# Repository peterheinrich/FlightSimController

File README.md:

# Overview
This small project implements a controller board intended for use in DIY flight simulator cockpits. The goal of the project is to create a versatile
hardware component suitable for a variety of simulated instruments (from buttons, dials and lights to glass cockpits), using a common bus 
interconnect and a common programming model and environment.

# Basic Requirements
- Flexible I/O (3.3 V digital I/O, high current H-bridge for stepper motors, analog input for sliders and potentiometers).
- Raspberry Pi CM4 connectors with HDMI/USB and parallel display connectors for resolutions (320x240 to 4k)
- RP2040 microcontroller for all low-spped I/O
- RS485 bus connector with integrated power supply via D-SUB-9 connector

# Current Project State
!!! EXPERIMENTAL, DESIGN ONLY !!!

Board Schematic:
[Schematic](/assets/FlightSimController-Schematics.pdf)

Rendered board view (front):

Rendered board view (back):

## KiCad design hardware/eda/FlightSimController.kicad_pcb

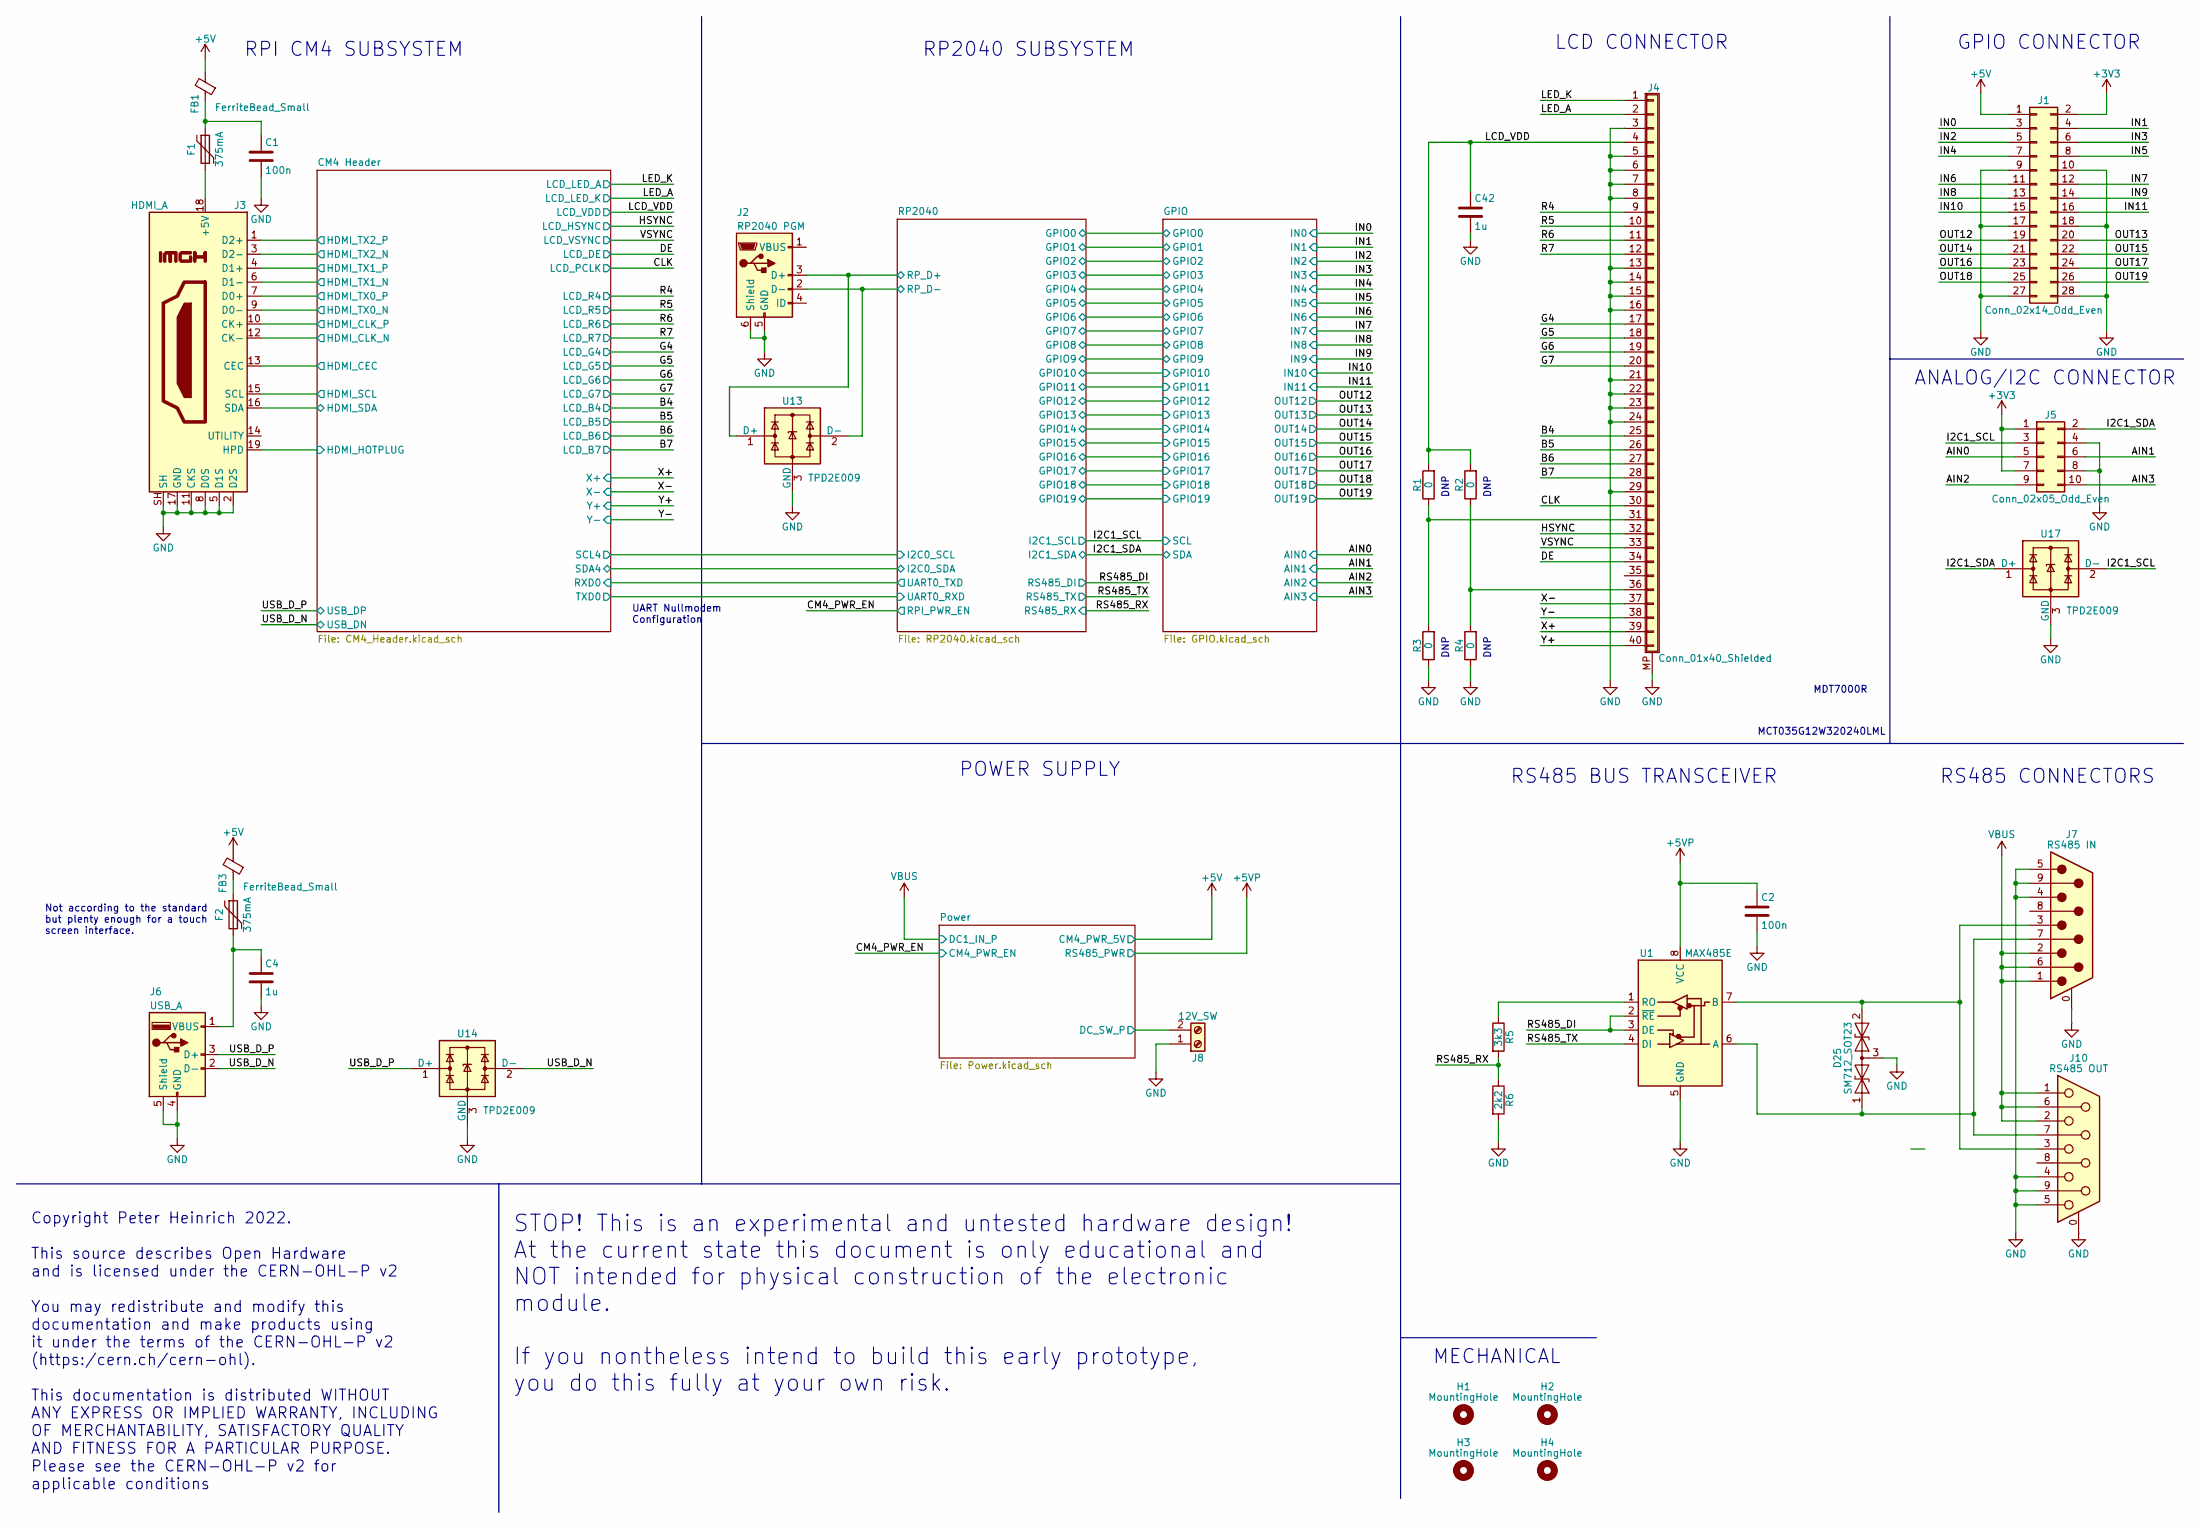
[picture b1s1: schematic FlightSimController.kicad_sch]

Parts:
C1, C2: 100n; C_0603_1608Metric_Pad1.08x0.95mm_HandSolder; MPN C0603C104K4RACTU
C4, C42: 1u; C_0603_1608Metric_Pad1.08x0.95mm_HandSolder; MPN CC0603KRX5R6BB105
D25: SM712_SOT23; SOT-23; MPN SM712-02HTG
F1, F2: 375mA; Fuse_1210_3225Metric_Pad1.42x2.65mm_HandSolder; MPN MCCFB1206TFF/375
FB1, FB3: FerriteBead_Small; L_0805_2012Metric; MPN BLM21PG221SN1D
H1, H2, H3, H4: MountingHole; MountingHole_3.2mm_M3_DIN965
J1: Conn_02x14_Odd_Even; PinHeader_2x14_P2.54mm_Vertical; MPN 68691-440HLF
J2: RP2040 PGM; USB_Micro-B_Wuerth_614105150721_Vertical_CircularHoles; MPN 614105150721
J3: HDMI_A; HDMI_A_Molex_208658-1001_Horizontal; MPN 208658-1001
J4: Conn_01x40_Shielded; TE_4-1734839-0_1x40-1MP_P0.5mm_Horizontal; MPN 4-1734839-0
J5: Conn_02x05_Odd_Even; PinHeader_2x05_P2.54mm_Vertical; MPN 826925-5
J6: USB_A; USB_A_Molex_67643_Horizontal; MPN 67643-0910
J7: RS485 IN; DSUB-9_Male_Vertical_P2.77x2.84mm_MountingHoles; MPN L777TSEG09POL2RM8
J8: 12V_SW; TerminalBlock_bornier-2_P5.08mm; MPN PM5.08/2/90 BLK
J10: RS485 OUT; DSUB-9_Female_Vertical_P2.77x2.84mm_MountingHoles; MPN L77TSEH09SOL2RM8
R1, R2, R3, R4: 0; R_0603_1608Metric_Pad0.98x0.95mm_HandSolder; MPN RC0603JR-070RL
R5: 3k3; R_0603_1608Metric_Pad0.98x0.95mm_HandSolder; MPN RC0603FR-073K3L
R6: 2k2; R_0603_1608Metric_Pad0.98x0.95mm_HandSolder; MPN RC0603FR-132K2L
U1: MAX485E; SOIC-8_3.9x4.9mm_P1.27mm; MPN MAX485CSA+
U13, U14, U17: TPD2E009; SOT-23; MPN TPD2E009DBZR

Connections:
+3V3: J1.2, J5.1, J5.7; also elsewhere on the board
+5V: FB1.2, FB3.2, J1.1; also elsewhere on the board
+5VP: C2.1, U1.8 (VCC); also elsewhere on the board
/AIN0: J5.5; also elsewhere on the board
/AIN1: J5.6; also elsewhere on the board
/AIN2: J5.9; also elsewhere on the board
/AIN3: J5.10; also elsewhere on the board
/B4: J4.25; also elsewhere on the board
/B5: J4.26; also elsewhere on the board
/B6: J4.27; also elsewhere on the board
/B7: J4.28; also elsewhere on the board
/CLK: J4.30; also elsewhere on the board
/CM4 Header/HDMI_CEC: J3.13 (CEC); also elsewhere on the board
/CM4 Header/HDMI_CLK_N: J3.12 (CK-); also elsewhere on the board
/CM4 Header/HDMI_CLK_P: J3.10 (CK+); also elsewhere on the board
/CM4 Header/HDMI_SCL: J3.15 (SCL); also elsewhere on the board
/CM4 Header/HDMI_SDA: J3.16 (SDA); also elsewhere on the board
/CM4 Header/HDMI_TX0_N: J3.9 (D0-); also elsewhere on the board
/CM4 Header/HDMI_TX0_P: J3.7 (D0+); also elsewhere on the board
/CM4 Header/HDMI_TX1_N: J3.6 (D1-); also elsewhere on the board
/CM4 Header/HDMI_TX1_P: J3.4 (D1+); also elsewhere on the board
/CM4 Header/HDMI_TX2_N: J3.3 (D2-); also elsewhere on the board
/CM4 Header/HDMI_TX2_P: J3.1 (D2+); also elsewhere on the board
/DE: J4.34; also elsewhere on the board
/G4: J4.17; also elsewhere on the board
/G5: J4.18; also elsewhere on the board
/G6: J4.19; also elsewhere on the board
/G7: J4.20; also elsewhere on the board
/HDMI_HOTPLUG: J3.19 (HPD)
/HSYNC: J4.32; also elsewhere on the board
/I2C1_SCL: J5.3, U17.2 (D-); also elsewhere on the board
/I2C1_SDA: J5.2, U17.1 (D+); also elsewhere on the board
/IN0: J1.3; also elsewhere on the board
/IN1: J1.4; also elsewhere on the board
/IN2: J1.5; also elsewhere on the board
/IN3: J1.6; also elsewhere on the board
/IN4: J1.7; also elsewhere on the board
/IN5: J1.8; also elsewhere on the board
/IN6: J1.11; also elsewhere on the board
/IN7: J1.12; also elsewhere on the board
/IN8: J1.13; also elsewhere on the board
/IN9: J1.14; also elsewhere on the board
/IN10: J1.15; also elsewhere on the board
/IN11: J1.16; also elsewhere on the board
/LCD_VDD: C42.1, J4.4, R1.2, R2.2; also elsewhere on the board
/LED_A: J4.2; also elsewhere on the board
/LED_K: J4.1; also elsewhere on the board
/OUT12: J1.19; also elsewhere on the board
/OUT13: J1.20; also elsewhere on the board
/OUT14: J1.21; also elsewhere on the board
/OUT15: J1.22; also elsewhere on the board
/OUT16: J1.23; also elsewhere on the board
/OUT17: J1.24; also elsewhere on the board
/OUT18: J1.25; also elsewhere on the board
/OUT19: J1.26; also elsewhere on the board
/Power/DC_SW_P: J8.2; also elsewhere on the board
/R4: J4.9; also elsewhere on the board
/R5: J4.10; also elsewhere on the board
/R6: J4.11; also elsewhere on the board
/R7: J4.12; also elsewhere on the board
/RP2040/RP_D+: J2.3 (D+), U13.1 (D+); also elsewhere on the board
/RP2040/RP_D-: J2.2 (D-), U13.2 (D-); also elsewhere on the board
/RS485_DI: U1.2 (~RE), U1.3 (DE); also elsewhere on the board
/RS485_RX: R5.2, R6.1; also elsewhere on the board
/RS485_TX: U1.4 (DI); also elsewhere on the board
/USB_D_N: J6.2 (D-), U14.2 (D-); also elsewhere on the board
/USB_D_P: J6.3 (D+), U14.1 (D+); also elsewhere on the board
/VSYNC: J4.33; also elsewhere on the board
/X+: J4.39; also elsewhere on the board
/X-: J4.37; also elsewhere on the board
/Y+: J4.40; also elsewhere on the board
/Y-: J4.38; also elsewhere on the board
GND: C1.2, C2.2, C4.2, C42.2, D25.3 (common), J1.9, J1.10, J1.17, J1.18, J1.27, J1.28, J2.5 (GND), J2.6 (Shield), J3.2 (D2S), J3.5 (D1S), J3.8 (D0S), J3.11 (CKS), J3.17 (GND), J3.SH, J4.3, J4.5, J4.6, J4.7, J4.8, J4.13, J4.14, J4.15, J4.16, J4.21, J4.22, J4.23, J4.24, J4.29, J4.MP (Shield), J5.4, J5.8, J6.4 (GND), J6.5 (Shield), J7.0 (PAD), J7.4, J7.5, J7.9, J8.1, J10.0 (PAD), J10.4, J10.5, J10.9, R3.1, R4.1, R6.2, U1.5 (GND), U13.3 (GND), U14.3 (GND), U17.3 (GND); also elsewhere on the board
unnamed: C1.1, F1.1, FB1.1
unnamed: C4.1, F2.2, J6.1 (VBUS)
unnamed: D25.1 (A1), J7.7, J10.7, U1.6 (A)
unnamed: D25.2 (A2), J7.3, J10.3, U1.7 (B)
unnamed: F1.2, J3.18 (+5V)
unnamed: F2.1, FB3.1
unnamed: J4.31, R1.1, R3.2
unnamed: J4.36, R2.1, R4.2
unnamed: R5.1, U1.1 (RO)
VBUS: J7.1, J7.2, J7.6, J10.1, J10.2, J10.6; also elsewhere on the board

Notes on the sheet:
UART Nullmodem Configuration
DNP
RPI CM4 SUBSYSTEM
MCT035G12W320240LML
LCD CONNECTOR
GPIO CONNECTOR
POWER SUPPLY
Not according to the standard but plenty enough for a touch screen interface.
Copyright Peter Heinrich 2022. This source describes Open Hardware and is licensed under the CERN-OHL-P v2 You may redistribute and modify this documentation and make products using it under the terms of the CERN-OHL-P v2 (https:/cern.ch/cern-ohl). This documentation is distributed WITHOUT ANY EXPR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
RS485 CONNECTORS
MDT7000R
MECHANICAL
ANALOG/I2C CONNECTOR
RS485 BUS TRANSCEIVER
RP2040 SUBSYSTEM
STOP! This is an experimental and untested hardware design! At the current state this document is only educational and NOT intended for physical construction of the electronic module. If you nontheless intend to build this early prototype, you do this fully at your own risk.

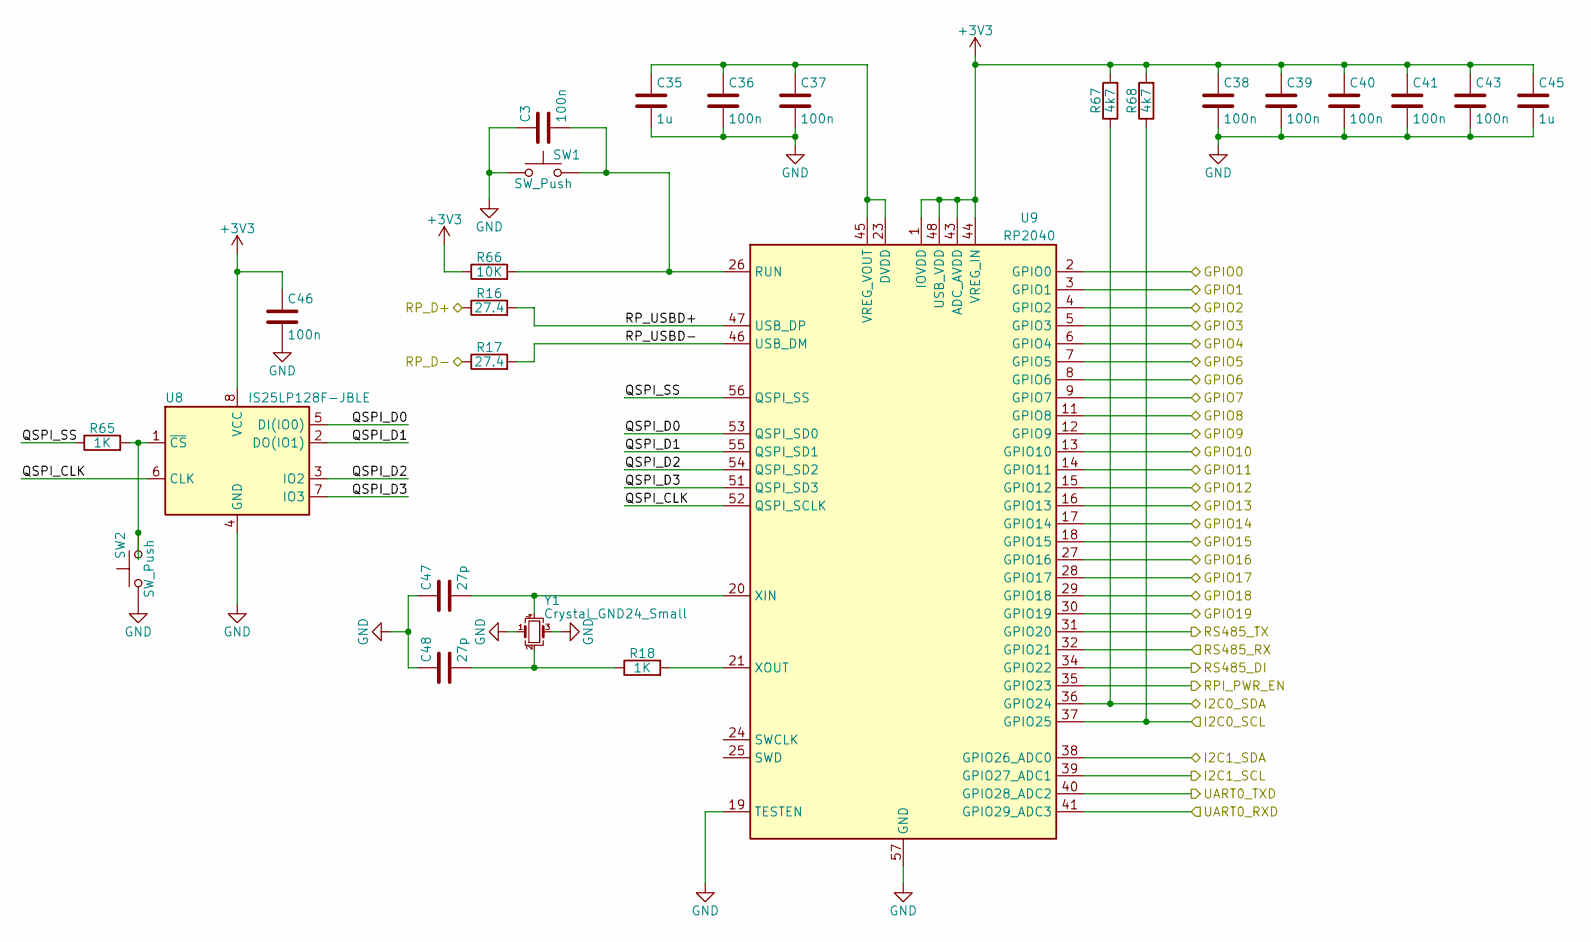
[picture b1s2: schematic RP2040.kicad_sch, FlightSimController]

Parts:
C3, C36, C37, C38, C39, C40, C41, C43, C46: 100n; C_0603_1608Metric_Pad1.08x0.95mm_HandSolder; MPN C0603C104K4RACTU
C35, C45: 1u; C_0603_1608Metric_Pad1.08x0.95mm_HandSolder; MPN CC0603KRX5R6BB105
C47, C48: 27p; C_0603_1608Metric_Pad1.08x0.95mm_HandSolder; MPN C0603C270K5GACTU
R16, R17: 27.4; R_0603_1608Metric_Pad0.98x0.95mm_HandSolder; MPN RC0603FR-0727R4L
R18, R65: 1K; R_0603_1608Metric_Pad0.98x0.95mm_HandSolder; MPN RC0603JR-071KL
R66: 10K; R_0603_1608Metric_Pad0.98x0.95mm_HandSolder; MPN RC0603FR-0710KL
R67, R68: 4k7; R_0603_1608Metric_Pad0.98x0.95mm_HandSolder; MPN RC0603FR-074K7L.
SW1, SW2: SW_Push; SW_Push_1P1T_NO_CK_KSC7xxJ; MPN KSC721J LFS
U8: IS25LP128F-JBLE; SOIC-8_5.23x5.23mm_P1.27mm; MPN IS25LP128F-JBLE
U9: RP2040; QFN-56-1EP_7x7mm_P0.4mm_EP3.2x3.2mm; MPN RP2040CT
Y1: Crystal_GND24_Small; Crystal_SMD_Abracon_ABM8G-4Pin_3.2x2.5mm; MPN ABM8G-12.000MHZ-18-D2Y-T

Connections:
+3V3: C38.1, C39.1, C40.1, C41.1, C43.1, C45.1, C46.1, R66.1, R67.2, R68.2, U8.8 (VCC), U9.1 (IOVDD), U9.10 (IOVDD), U9.22 (IOVDD), U9.33 (IOVDD), U9.42 (IOVDD), U9.43 (ADC_AVDD), U9.44 (VREG_IN), U9.48 (USB_VDD), U9.49 (IOVDD); also elsewhere on the board
/CM4 Header/RXD0: U9.40 (GPIO28_ADC2); also elsewhere on the board
/CM4 Header/SCL4: R68.1, U9.37 (GPIO25); also elsewhere on the board
/CM4 Header/SDA4: R67.1, U9.36 (GPIO24); also elsewhere on the board
/CM4 Header/TXD0: U9.41 (GPIO29_ADC3); also elsewhere on the board
/CM4_PWR_EN: U9.35 (GPIO23); also elsewhere on the board
/GPIO/GPIO0: U9.2 (GPIO0); also elsewhere on the board
/GPIO/GPIO1: U9.3 (GPIO1); also elsewhere on the board
/GPIO/GPIO2: U9.4 (GPIO2); also elsewhere on the board
/GPIO/GPIO3: U9.5 (GPIO3); also elsewhere on the board
/GPIO/GPIO4: U9.6 (GPIO4); also elsewhere on the board
/GPIO/GPIO5: U9.7 (GPIO5); also elsewhere on the board
/GPIO/GPIO6: U9.8 (GPIO6); also elsewhere on the board
/GPIO/GPIO7: U9.9 (GPIO7); also elsewhere on the board
/GPIO/GPIO8: U9.11 (GPIO8); also elsewhere on the board
/GPIO/GPIO9: U9.12 (GPIO9); also elsewhere on the board
/GPIO/GPIO10: U9.13 (GPIO10); also elsewhere on the board
/GPIO/GPIO11: U9.14 (GPIO11); also elsewhere on the board
/GPIO/GPIO12: U9.15 (GPIO12); also elsewhere on the board
/GPIO/GPIO13: U9.16 (GPIO13); also elsewhere on the board
/GPIO/GPIO14: U9.17 (GPIO14); also elsewhere on the board
/GPIO/GPIO15: U9.18 (GPIO15); also elsewhere on the board
/GPIO/GPIO16: U9.27 (GPIO16); also elsewhere on the board
/GPIO/GPIO17: U9.28 (GPIO17); also elsewhere on the board
/GPIO/GPIO18: U9.29 (GPIO18); also elsewhere on the board
/GPIO/GPIO19: U9.30 (GPIO19); also elsewhere on the board
/I2C1_SCL: U9.39 (GPIO27_ADC1); also elsewhere on the board
/I2C1_SDA: U9.38 (GPIO26_ADC0); also elsewhere on the board
/RP2040/QSPI_CLK: U8.6 (CLK), U9.52 (QSPI_SCLK)
/RP2040/QSPI_D0: U8.5 (DI(IO0)), U9.53 (QSPI_SD0)
/RP2040/QSPI_D1: U8.2 (DO(IO1)), U9.55 (QSPI_SD1)
/RP2040/QSPI_D2: U8.3 (IO2), U9.54 (QSPI_SD2)
/RP2040/QSPI_D3: U8.7 (IO3), U9.51 (QSPI_SD3)
/RP2040/QSPI_SS: R65.1, U9.56 (QSPI_SS)
/RP2040/RP_D+: R16.1; also elsewhere on the board
/RP2040/RP_D-: R17.1; also elsewhere on the board
/RP2040/RP_USBD+: R16.2, U9.47 (USB_DP)
/RP2040/RP_USBD-: R17.2, U9.46 (USB_DM)
/RS485_DI: U9.34 (GPIO22); also elsewhere on the board
/RS485_RX: U9.32 (GPIO21); also elsewhere on the board
/RS485_TX: U9.31 (GPIO20); also elsewhere on the board
GND: C3.1, C35.2, C36.2, C37.2, C38.2, C39.2, C40.2, C41.2, C43.2, C45.2, C46.2, C47.1, C48.1, SW1.1, SW2.1, U8.4 (GND), U9.19 (TESTEN), U9.57 (GND), Y1.1, Y1.3; also elsewhere on the board
unnamed: C3.2, R66.2, SW1.2, U9.26 (RUN)
unnamed: C35.1, C36.1, C37.1, U9.23 (DVDD), U9.45 (VREG_VOUT), U9.50 (DVDD)
unnamed: C47.2, U9.20 (XIN), Y1.4
unnamed: C48.2, R18.1, Y1.2
unnamed: R18.2, U9.21 (XOUT)
unnamed: R65.2, SW2.2, U8.1 (~CS)

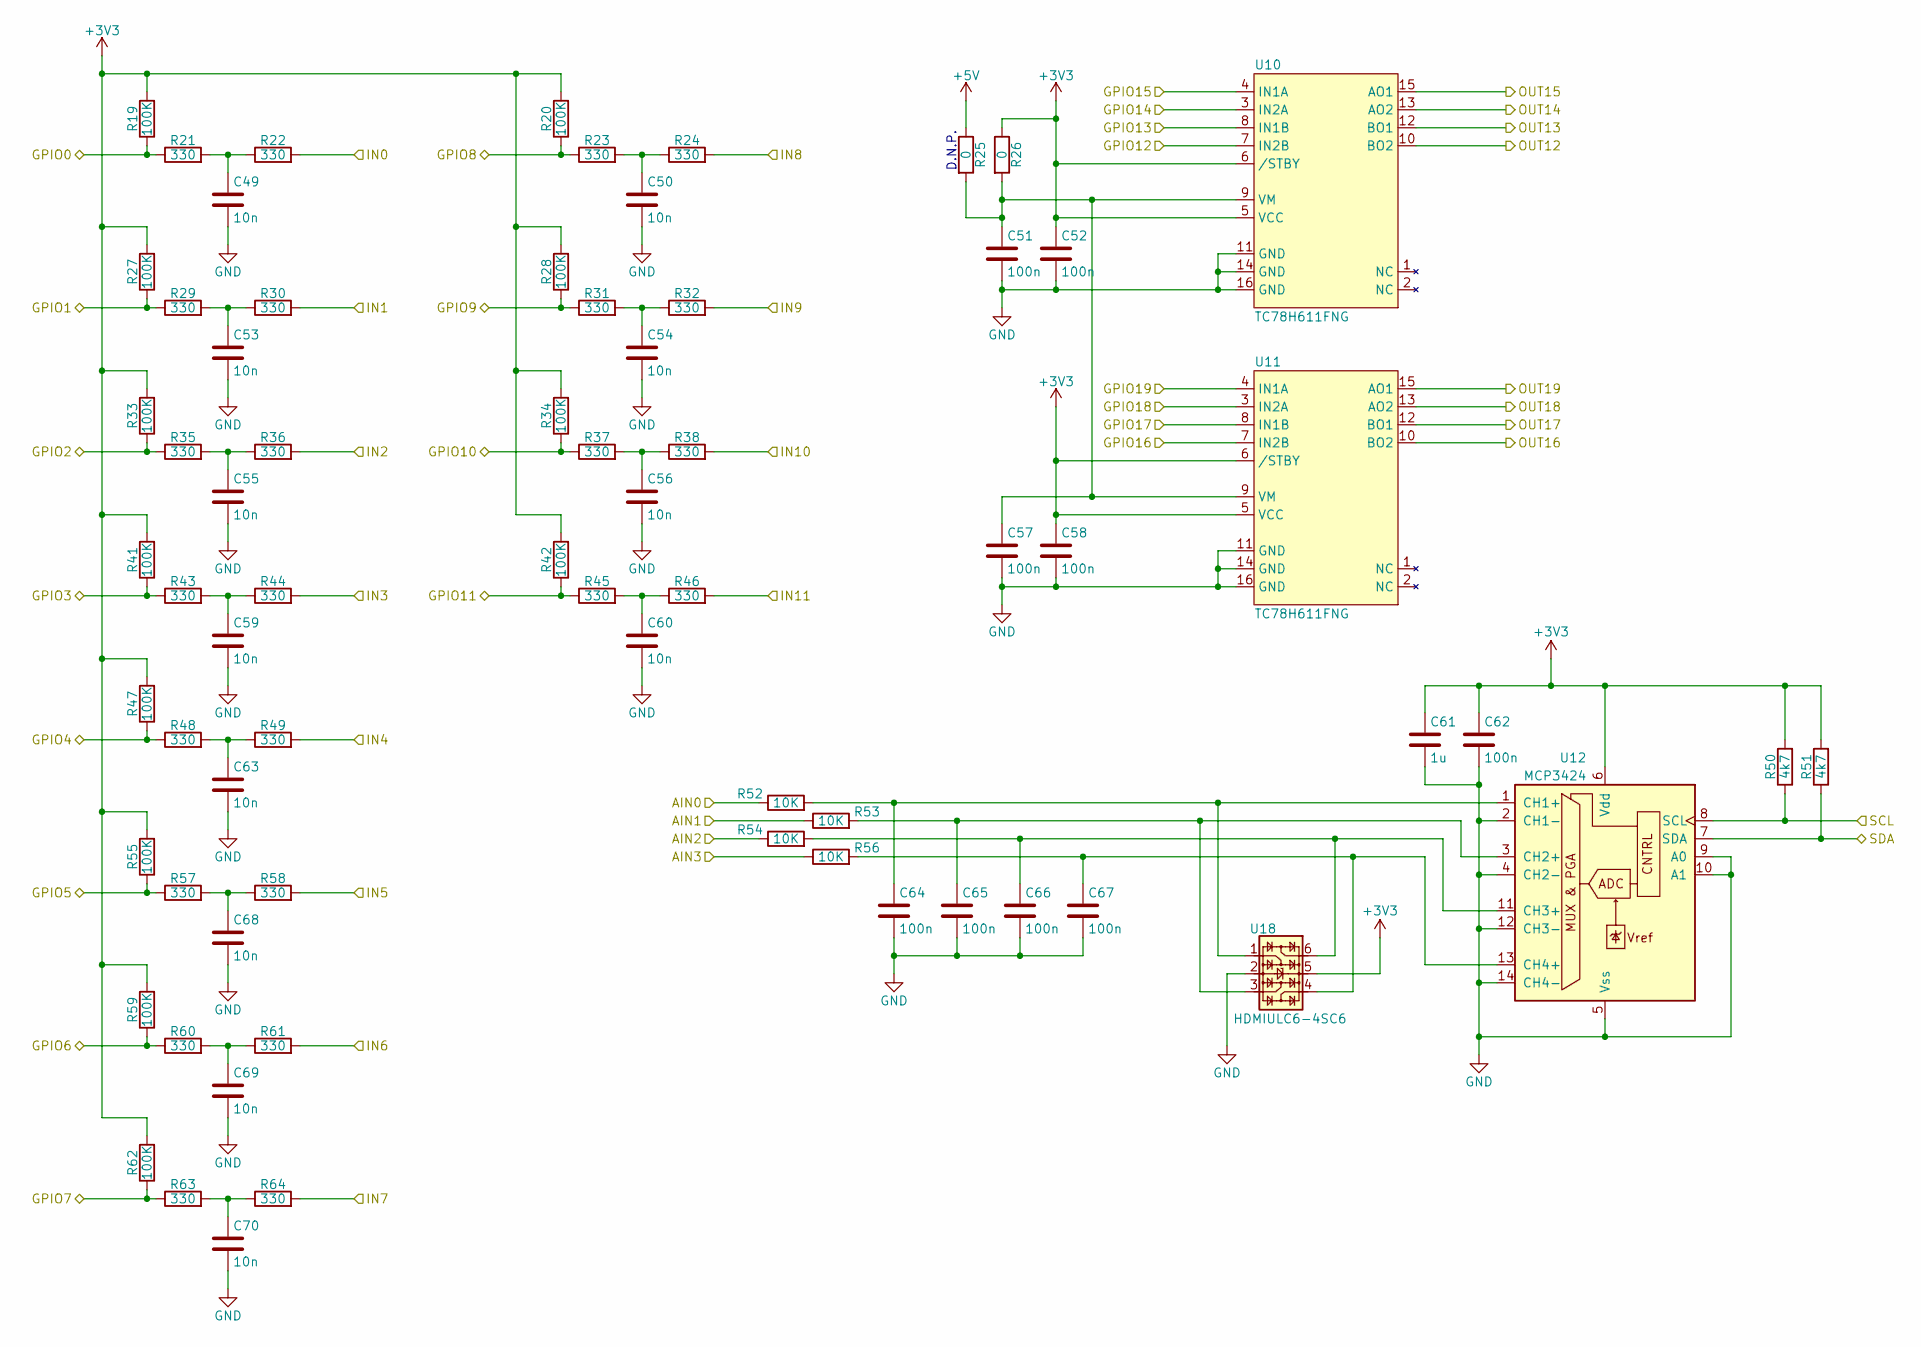
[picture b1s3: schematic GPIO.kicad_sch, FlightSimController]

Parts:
C49, C50, C53, C54, C55, C56, C59, C60, C63, C68, C69, C70: 10n; C_0603_1608Metric_Pad1.08x0.95mm_HandSolder; MPN CC0603KRX7R9BB103
C51, C52, C57, C58, C62, C64, C65, C66, C67: 100n; C_0603_1608Metric_Pad1.08x0.95mm_HandSolder; MPN C0603C104K4RACTU
C61: 1u; C_0603_1608Metric_Pad1.08x0.95mm_HandSolder; MPN CC0603KRX5R6BB105
R19, R20, R27, R28, R33, R34, R41, R42, R47, R55, R59, R62: 100K; R_0603_1608Metric_Pad0.98x0.95mm_HandSolder; MPN RC0603FR-13100KL
R21, R22, R23, R24, R29, R30, R31, R32, R35, R36, R37, R38, R43, R44, R45, R46, R48, R49, R57, R58, R60, R61, R63, R64: 330; R_0603_1608Metric_Pad0.98x0.95mm_HandSolder; MPN RC0603FR-07330RL
R25, R26: 0; R_0603_1608Metric_Pad0.98x0.95mm_HandSolder; MPN RC0603JR-070RL
R50, R51: 4k7; R_0603_1608Metric_Pad0.98x0.95mm_HandSolder; MPN RC0603FR-074K7L.
R52, R53, R54, R56: 10K; R_0603_1608Metric_Pad0.98x0.95mm_HandSolder; MPN RC0603FR-0710KL
U10, U11: TC78H611FNG; TSSOP-16_4.4x5mm_P0.65mm; MPN TC78H611FNG(O,EL)
U12: MCP3424; SOIC-14_3.9x8.7mm_P1.27mm; MPN MCP3424-E/SL
U18: HDMIULC6-4SC6; SOT-23-6; MPN HDMIULC6-4SC6

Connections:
+3V3: C52.1, C58.1, C61.1, C62.1, R19.2, R20.2, R26.1, R27.2, R28.2, R33.2, R34.2, R41.2, R42.2, R47.2, R50.2, R51.2, R55.2, R59.2, R62.2, U10.5 (VCC), U10.6 (/STBY), U11.5 (VCC), U11.6 (/STBY), U12.6 (Vdd), U18.5; also elsewhere on the board
+5V: R25.1; also elsewhere on the board
/AIN0: R52.1; also elsewhere on the board
/AIN1: R53.1; also elsewhere on the board
/AIN2: R54.1; also elsewhere on the board
/AIN3: R56.1; also elsewhere on the board
/GPIO/GPIO0: R19.1, R21.1; also elsewhere on the board
/GPIO/GPIO1: R27.1, R29.1; also elsewhere on the board
/GPIO/GPIO2: R33.1, R35.1; also elsewhere on the board
/GPIO/GPIO3: R41.1, R43.1; also elsewhere on the board
/GPIO/GPIO4: R47.1, R48.1; also elsewhere on the board
/GPIO/GPIO5: R55.1, R57.1; also elsewhere on the board
/GPIO/GPIO6: R59.1, R60.1; also elsewhere on the board
/GPIO/GPIO7: R62.1, R63.1; also elsewhere on the board
/GPIO/GPIO8: R20.1, R23.1; also elsewhere on the board
/GPIO/GPIO9: R28.1, R31.1; also elsewhere on the board
/GPIO/GPIO10: R34.1, R37.1; also elsewhere on the board
/GPIO/GPIO11: R42.1, R45.1; also elsewhere on the board
/GPIO/GPIO12: U10.7 (IN2B); also elsewhere on the board
/GPIO/GPIO13: U10.8 (IN1B); also elsewhere on the board
/GPIO/GPIO14: U10.3 (IN2A); also elsewhere on the board
/GPIO/GPIO15: U10.4 (IN1A); also elsewhere on the board
/GPIO/GPIO16: U11.7 (IN2B); also elsewhere on the board
/GPIO/GPIO17: U11.8 (IN1B); also elsewhere on the board
/GPIO/GPIO18: U11.3 (IN2A); also elsewhere on the board
/GPIO/GPIO19: U11.4 (IN1A); also elsewhere on the board
/I2C1_SCL: R50.1, U12.8 (SCL); also elsewhere on the board
/I2C1_SDA: R51.1, U12.7 (SDA); also elsewhere on the board
/IN0: R22.2; also elsewhere on the board
/IN1: R30.2; also elsewhere on the board
/IN2: R36.2; also elsewhere on the board
/IN3: R44.2; also elsewhere on the board
/IN4: R49.2; also elsewhere on the board
/IN5: R58.2; also elsewhere on the board
/IN6: R61.2; also elsewhere on the board
/IN7: R64.2; also elsewhere on the board
/IN8: R24.2; also elsewhere on the board
/IN9: R32.2; also elsewhere on the board
/IN10: R38.2; also elsewhere on the board
/IN11: R46.2; also elsewhere on the board
/OUT12: U10.10 (BO2); also elsewhere on the board
/OUT13: U10.12 (BO1); also elsewhere on the board
/OUT14: U10.13 (AO2); also elsewhere on the board
/OUT15: U10.15 (AO1); also elsewhere on the board
/OUT16: U11.10 (BO2); also elsewhere on the board
/OUT17: U11.12 (BO1); also elsewhere on the board
/OUT18: U11.13 (AO2); also elsewhere on the board
/OUT19: U11.15 (AO1); also elsewhere on the board
GND: C49.2, C50.2, C51.2, C52.2, C53.2, C54.2, C55.2, C56.2, C57.2, C58.2, C59.2, C60.2, C61.2, C62.2, C63.2, C64.2, C65.2, C66.2, C67.2, C68.2, C69.2, C70.2, U10.11 (GND), U10.14 (GND), U10.16 (GND), U11.11 (GND), U11.14 (GND), U11.16 (GND), U12.2 (CH1-), U12.4 (CH2-), U12.5 (Vss), U12.9 (A0), U12.10 (A1), U12.12 (CH3-), U12.14 (CH4-), U18.2; also elsewhere on the board
unnamed: C49.1, R21.2, R22.1
unnamed: C50.1, R23.2, R24.1
unnamed: C51.1, C57.1, R25.2, R26.2, U10.9 (VM), U11.9 (VM)
unnamed: C53.1, R29.2, R30.1
unnamed: C54.1, R31.2, R32.1
unnamed: C55.1, R35.2, R36.1
unnamed: C56.1, R37.2, R38.1
unnamed: C59.1, R43.2, R44.1
unnamed: C60.1, R45.2, R46.1
unnamed: C63.1, R48.2, R49.1
unnamed: C64.1, R52.2, U12.1 (CH1+), U18.1
unnamed: C65.1, R53.2, U12.3 (CH2+), U18.3
unnamed: C66.1, R54.2, U12.11 (CH3+), U18.6
unnamed: C67.1, R56.2, U12.13 (CH4+), U18.4
unnamed: C68.1, R57.2, R58.1
unnamed: C69.1, R60.2, R61.1
unnamed: C70.1, R63.2, R64.1

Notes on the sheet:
D.N.P.

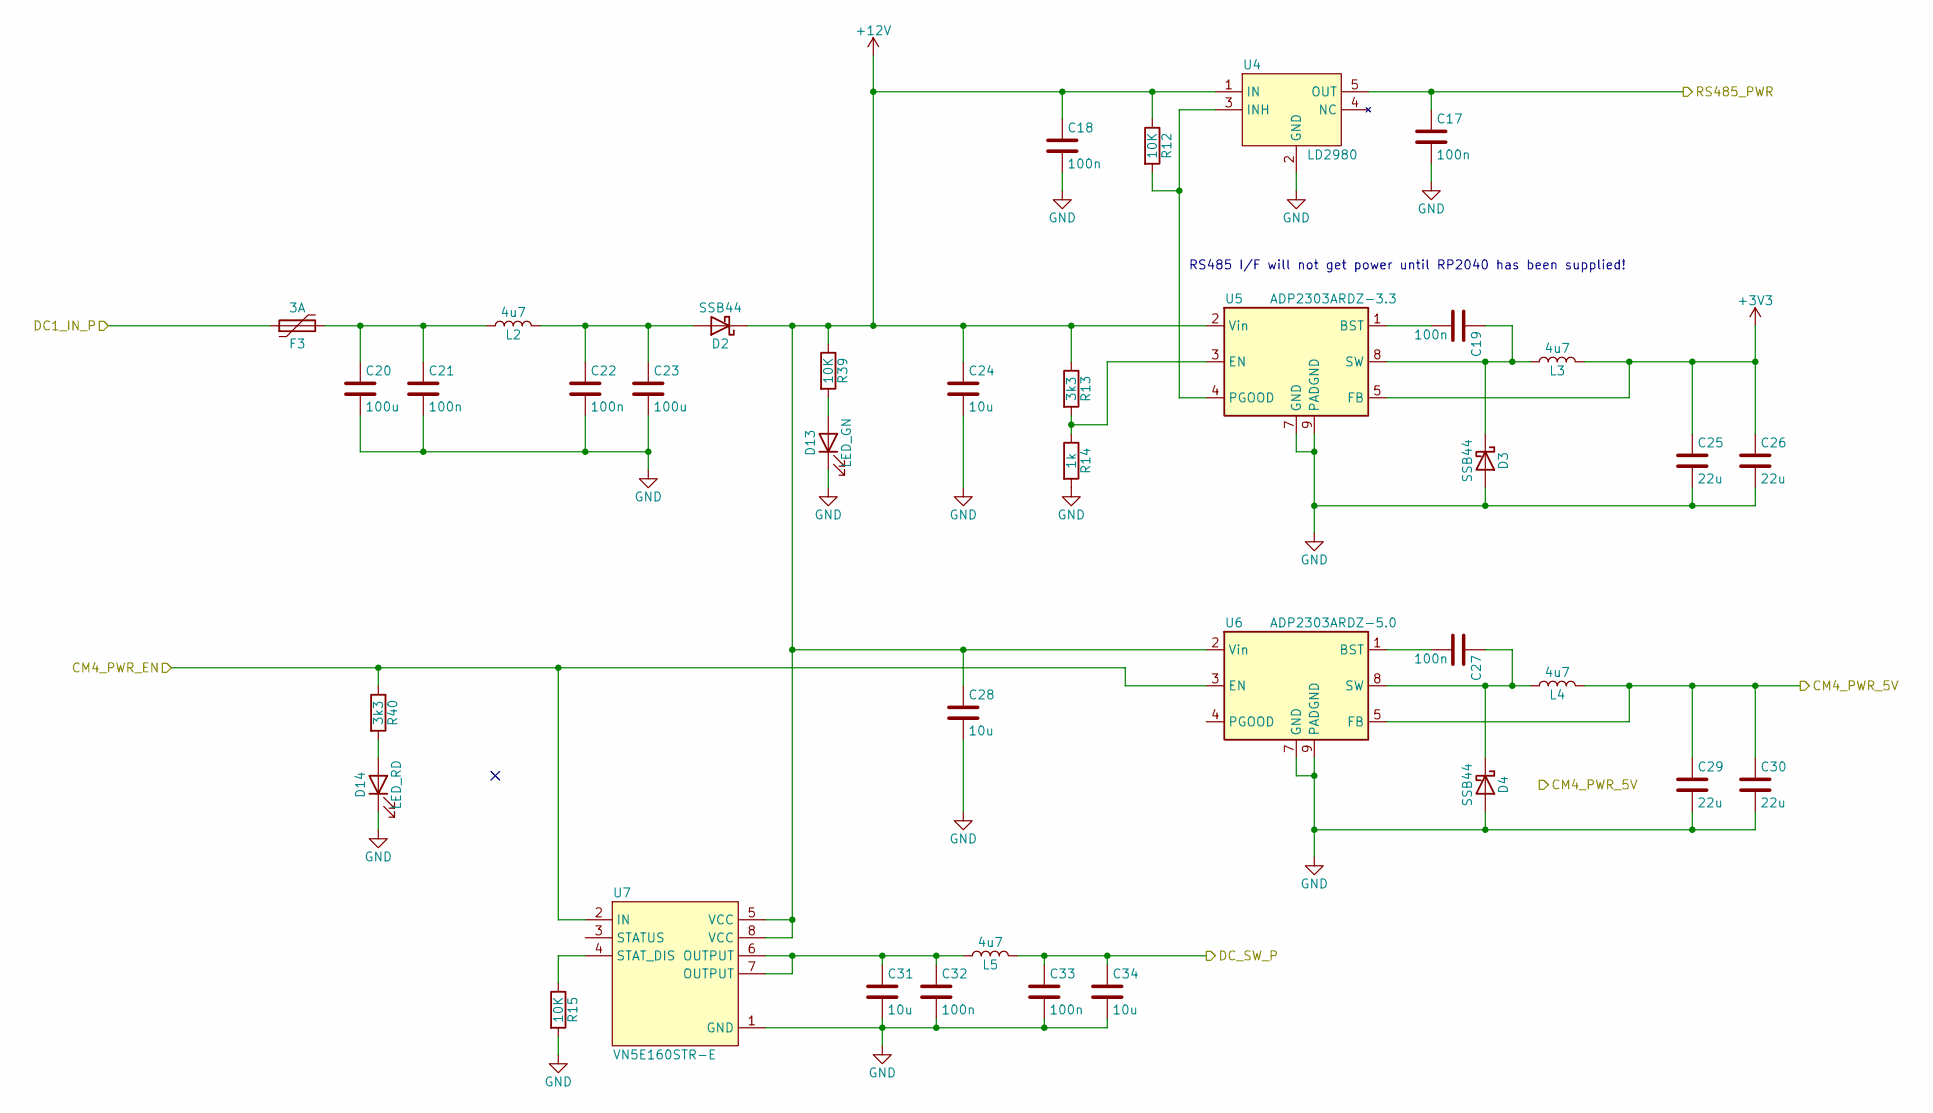
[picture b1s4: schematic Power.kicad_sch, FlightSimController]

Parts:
C17, C18, C19, C21, C22, C27, C32, C33: 100n; C_0603_1608Metric_Pad1.08x0.95mm_HandSolder; MPN C0603C104K4RACTU
C20, C23: 100u; C_1210_3225Metric; MPN EMK325ABJ107MM-T
C24, C28, C31, C34: 10u; C_0805_2012Metric_Pad1.18x1.45mm_HandSolder; MPN GRM21BR61C106KE15L
C25, C26, C29, C30: 22u; C_0805_2012Metric_Pad1.18x1.45mm_HandSolder; MPN GRM21BR61E226ME44L
D2, D3, D4: SSB44; D_SMB; MPN SSB44-E3/52T
D13: LED_GN; LED_0805_2012Metric_Pad1.15x1.40mm_HandSolder; MPN MP008279
D14: LED_RD; LED_0805_2012Metric_Pad1.15x1.40mm_HandSolder; MPN MP008293
F3: 3A; Fuse_1210_3225Metric_Pad1.42x2.65mm_HandSolder; MPN SF-1206S300-2
L2, L3, L4, L5: 4u7; L_Vishay_IHLP-2020; MPN IHLP2020BZER4R7M01
R12, R15, R39: 10K; R_0603_1608Metric_Pad0.98x0.95mm_HandSolder; MPN RC0603FR-0710KL
R13, R40: 3k3; R_0603_1608Metric_Pad0.98x0.95mm_HandSolder; MPN RC0603FR-073K3L
R14: 1k; R_0603_1608Metric_Pad0.98x0.95mm_HandSolder; MPN RC0603FR-071KP
U4: LD2980; SOT-23-5_HandSoldering; MPN LD2980ABM50TR
U5: ADP2303ARDZ-3.3; SOIC-8-1EP_3.9x4.9mm_P1.27mm_EP2.29x3mm_ThermalVias; MPN ADP2303ARDZ-3.3-R7
U6: ADP2303ARDZ-5.0; SOIC-8-1EP_3.9x4.9mm_P1.27mm_EP2.29x3mm_ThermalVias; MPN ADP2303ARDZ-5.0-R7
U7: VN5E160STR-E; SOIC-8_3.9x4.9mm_P1.27mm; MPN VN5E160STR-E

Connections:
+3V3: C25.1, C26.1, L3.2, U5.5 (FB); also elsewhere on the board
+5V: C29.1, C30.1, L4.2, U6.5 (FB); also elsewhere on the board
+5VP: C17.1, U4.5 (OUT); also elsewhere on the board
+12V: C18.1, C24.1, C28.1, D2.1 (K), R12.1, R13.1, R39.1, U4.1 (IN), U5.2 (Vin), U6.2 (Vin), U7.5 (VCC), U7.8 (VCC)
/CM4_PWR_EN: R40.1, U6.3 (EN), U7.2 (IN); also elsewhere on the board
/Power/DC_SW_P: C33.1, C34.1, L5.2; also elsewhere on the board
GND: C17.2, C18.2, C20.2, C21.2, C22.2, C23.2, C24.2, C25.2, C26.2, C28.2, C29.2, C30.2, C31.2, C32.2, C33.2, C34.2, D3.2 (A), D4.2 (A), D13.1 (K), D14.1 (K), R14.2, R15.2, U4.2 (GND), U5.7 (GND), U5.9 (PADGND), U6.7 (GND), U6.9 (PADGND), U7.1 (GND); also elsewhere on the board
unnamed: C19.1, D3.1 (K), L3.1, U5.8 (SW)
unnamed: C19.2, U5.1 (BST)
unnamed: C20.1, C21.1, F3.2, L2.1
unnamed: C22.1, C23.1, D2.2 (A), L2.2
unnamed: C27.1, D4.1 (K), L4.1, U6.8 (SW)
unnamed: C27.2, U6.1 (BST)
unnamed: C31.1, C32.1, L5.1, U7.6 (OUTPUT), U7.7 (OUTPUT)
unnamed: D13.2 (A), R39.2
unnamed: D14.2 (A), R40.2
unnamed: R12.2, U4.3 (INH), U5.4 (PGOOD)
unnamed: R13.2, R14.1, U5.3 (EN)
unnamed: R15.1, U7.4 (STAT_DIS)
VBUS: F3.1; also elsewhere on the board

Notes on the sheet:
RS485 I/F will not get power until RP2040 has been supplied!

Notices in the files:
hardware/eda/CM4_Header.kicad_sch:
License: CERN-OHL-P v2
hardware/eda/FlightSimController.kicad_pcb:
Licesne: CERN-OHL-P v2
Copytight © 2022
